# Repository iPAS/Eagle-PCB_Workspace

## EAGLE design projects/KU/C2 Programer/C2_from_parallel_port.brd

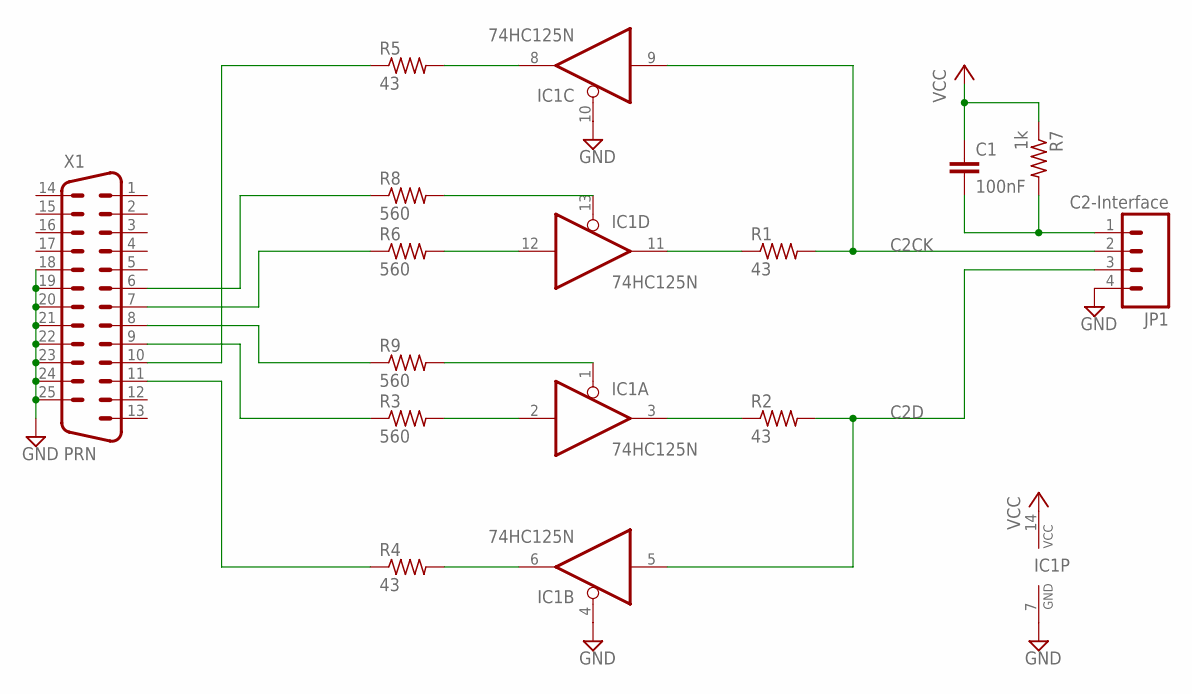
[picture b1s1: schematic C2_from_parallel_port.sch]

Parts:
C1: 100nF; RCL_C050-025X075
IC1: 74HC125N; DIL14
JP1: C2-Interface; MOLEX-1X4
R1, R2, R4, R5: 43; RCL_0204V
R3, R6, R8, R9: 560; RCL_0204V
R7: 1k; RCL_0204V
X1: PRN; M25D

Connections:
C2CK: IC1.9 (I), JP1.2, R1.2
C2D: IC1.5 (I), JP1.3, R2.2
GND: IC1.4 (OE), IC1.7 (GND), IC1.10 (OE), JP1.4, X1.18, X1.19, X1.20, X1.21, X1.22, X1.23, X1.24, X1.25
unnamed: IC1.8 (O), R5.2
unnamed: IC1.13 (OE), R8.2
unnamed: IC1.12 (I), R6.2
unnamed: IC1.1 (OE), R9.2
unnamed: IC1.2 (I), R3.2
unnamed: IC1.6 (O), R4.2
unnamed: R8.1, X1.6
unnamed: R6.1, X1.7
unnamed: R9.1, X1.8
unnamed: R3.1, X1.9
unnamed: R4.1, X1.11
unnamed: R5.1, X1.10
unnamed: IC1.11 (O), R1.1
unnamed: IC1.3 (O), R2.1
unnamed: C1.2, JP1.1, R7.2
VCC: C1.1, IC1.14 (VCC), R7.1

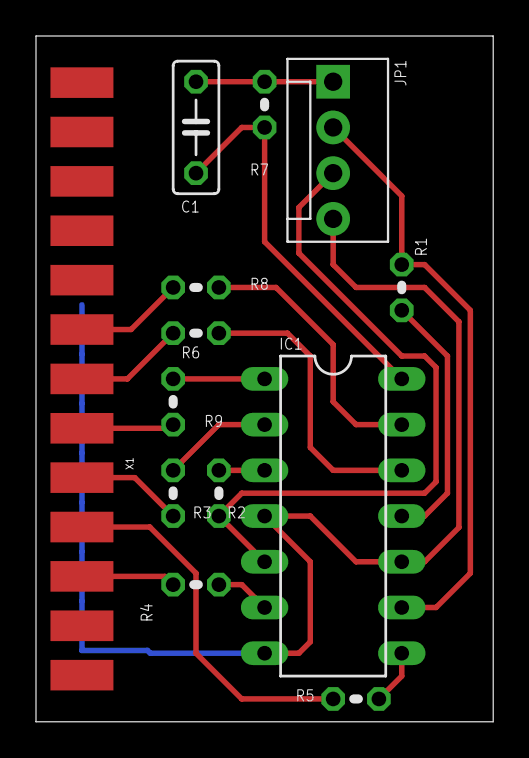
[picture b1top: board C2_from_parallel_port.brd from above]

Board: 2 copper layers, 25.4 x 38.1 mm, 13 parts (0 on the bottom side), 19 nets.

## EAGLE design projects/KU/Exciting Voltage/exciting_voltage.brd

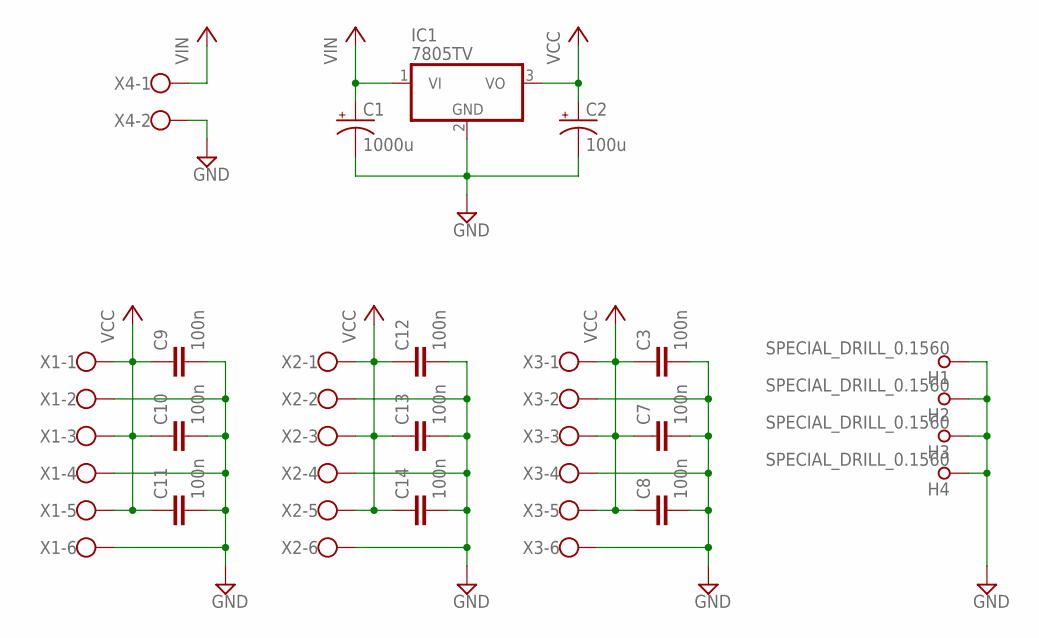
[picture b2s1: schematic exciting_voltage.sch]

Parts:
C1: 1000u; RCL_E5-13
C2: 100u; RCL_E2,5-7
C3, C7, C8, C9, C10, C11, C12, C13, C14: 100n; RCL_C050-025X075
H1, H2, H3, H4: SPECIAL_DRILL_0.1560; PAD_0.1560
IC1: 7805TV; TO220V
X1, X2, X3: 5EHDRC-6P
X4: 5EHDRC-2P

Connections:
GND: C1.-, C2.-, C3.2, C7.2, C8.2, C9.2, C10.2, C11.2, C12.2, C13.2, C14.2, H1.1, H2.1, H3.1, H4.1, IC1.2 (GND), X1.2, X1.4, X1.6, X2.2, X2.4, X2.6, X3.2, X3.4, X3.6, X4.2
VCC: C2.+, C3.1, C7.1, C8.1, C9.1, C10.1, C11.1, C12.1, C13.1, C14.1, IC1.3 (VO), X1.1, X1.3, X1.5, X2.1, X2.3, X2.5, X3.1, X3.3, X3.5
VIN: C1.+, IC1.1 (VI), X4.1

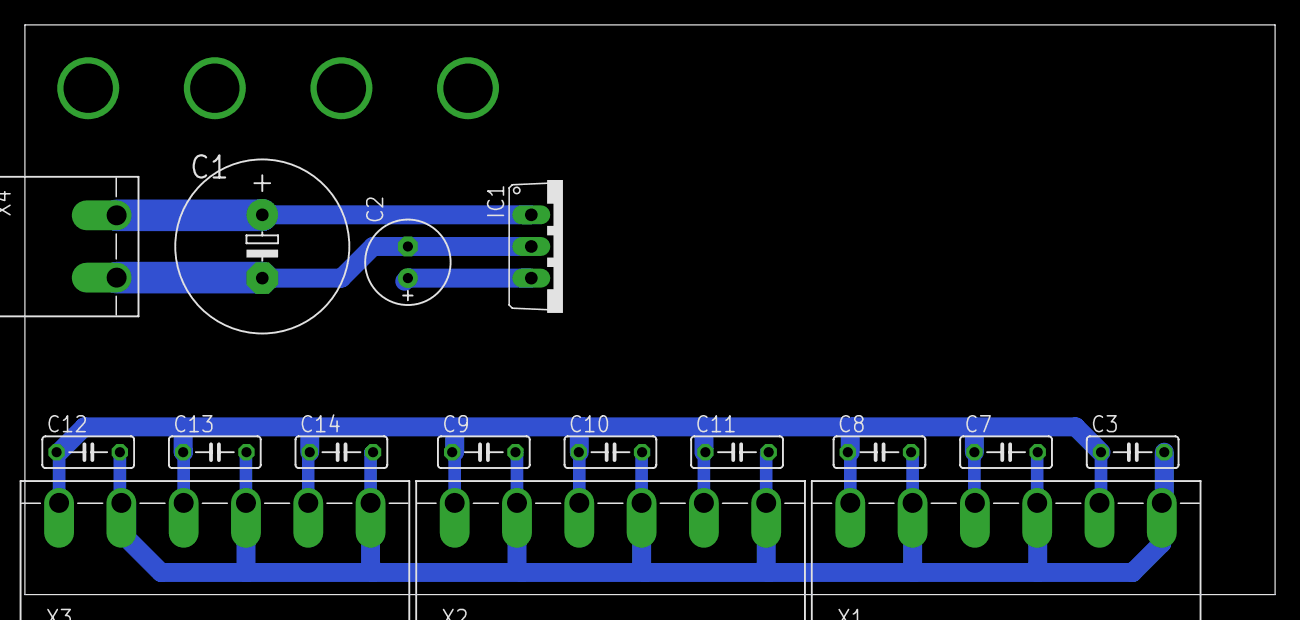
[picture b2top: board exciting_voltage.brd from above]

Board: 2 copper layers, 100.3 x 45.7 mm, 20 parts (0 on the bottom side), 3 nets.

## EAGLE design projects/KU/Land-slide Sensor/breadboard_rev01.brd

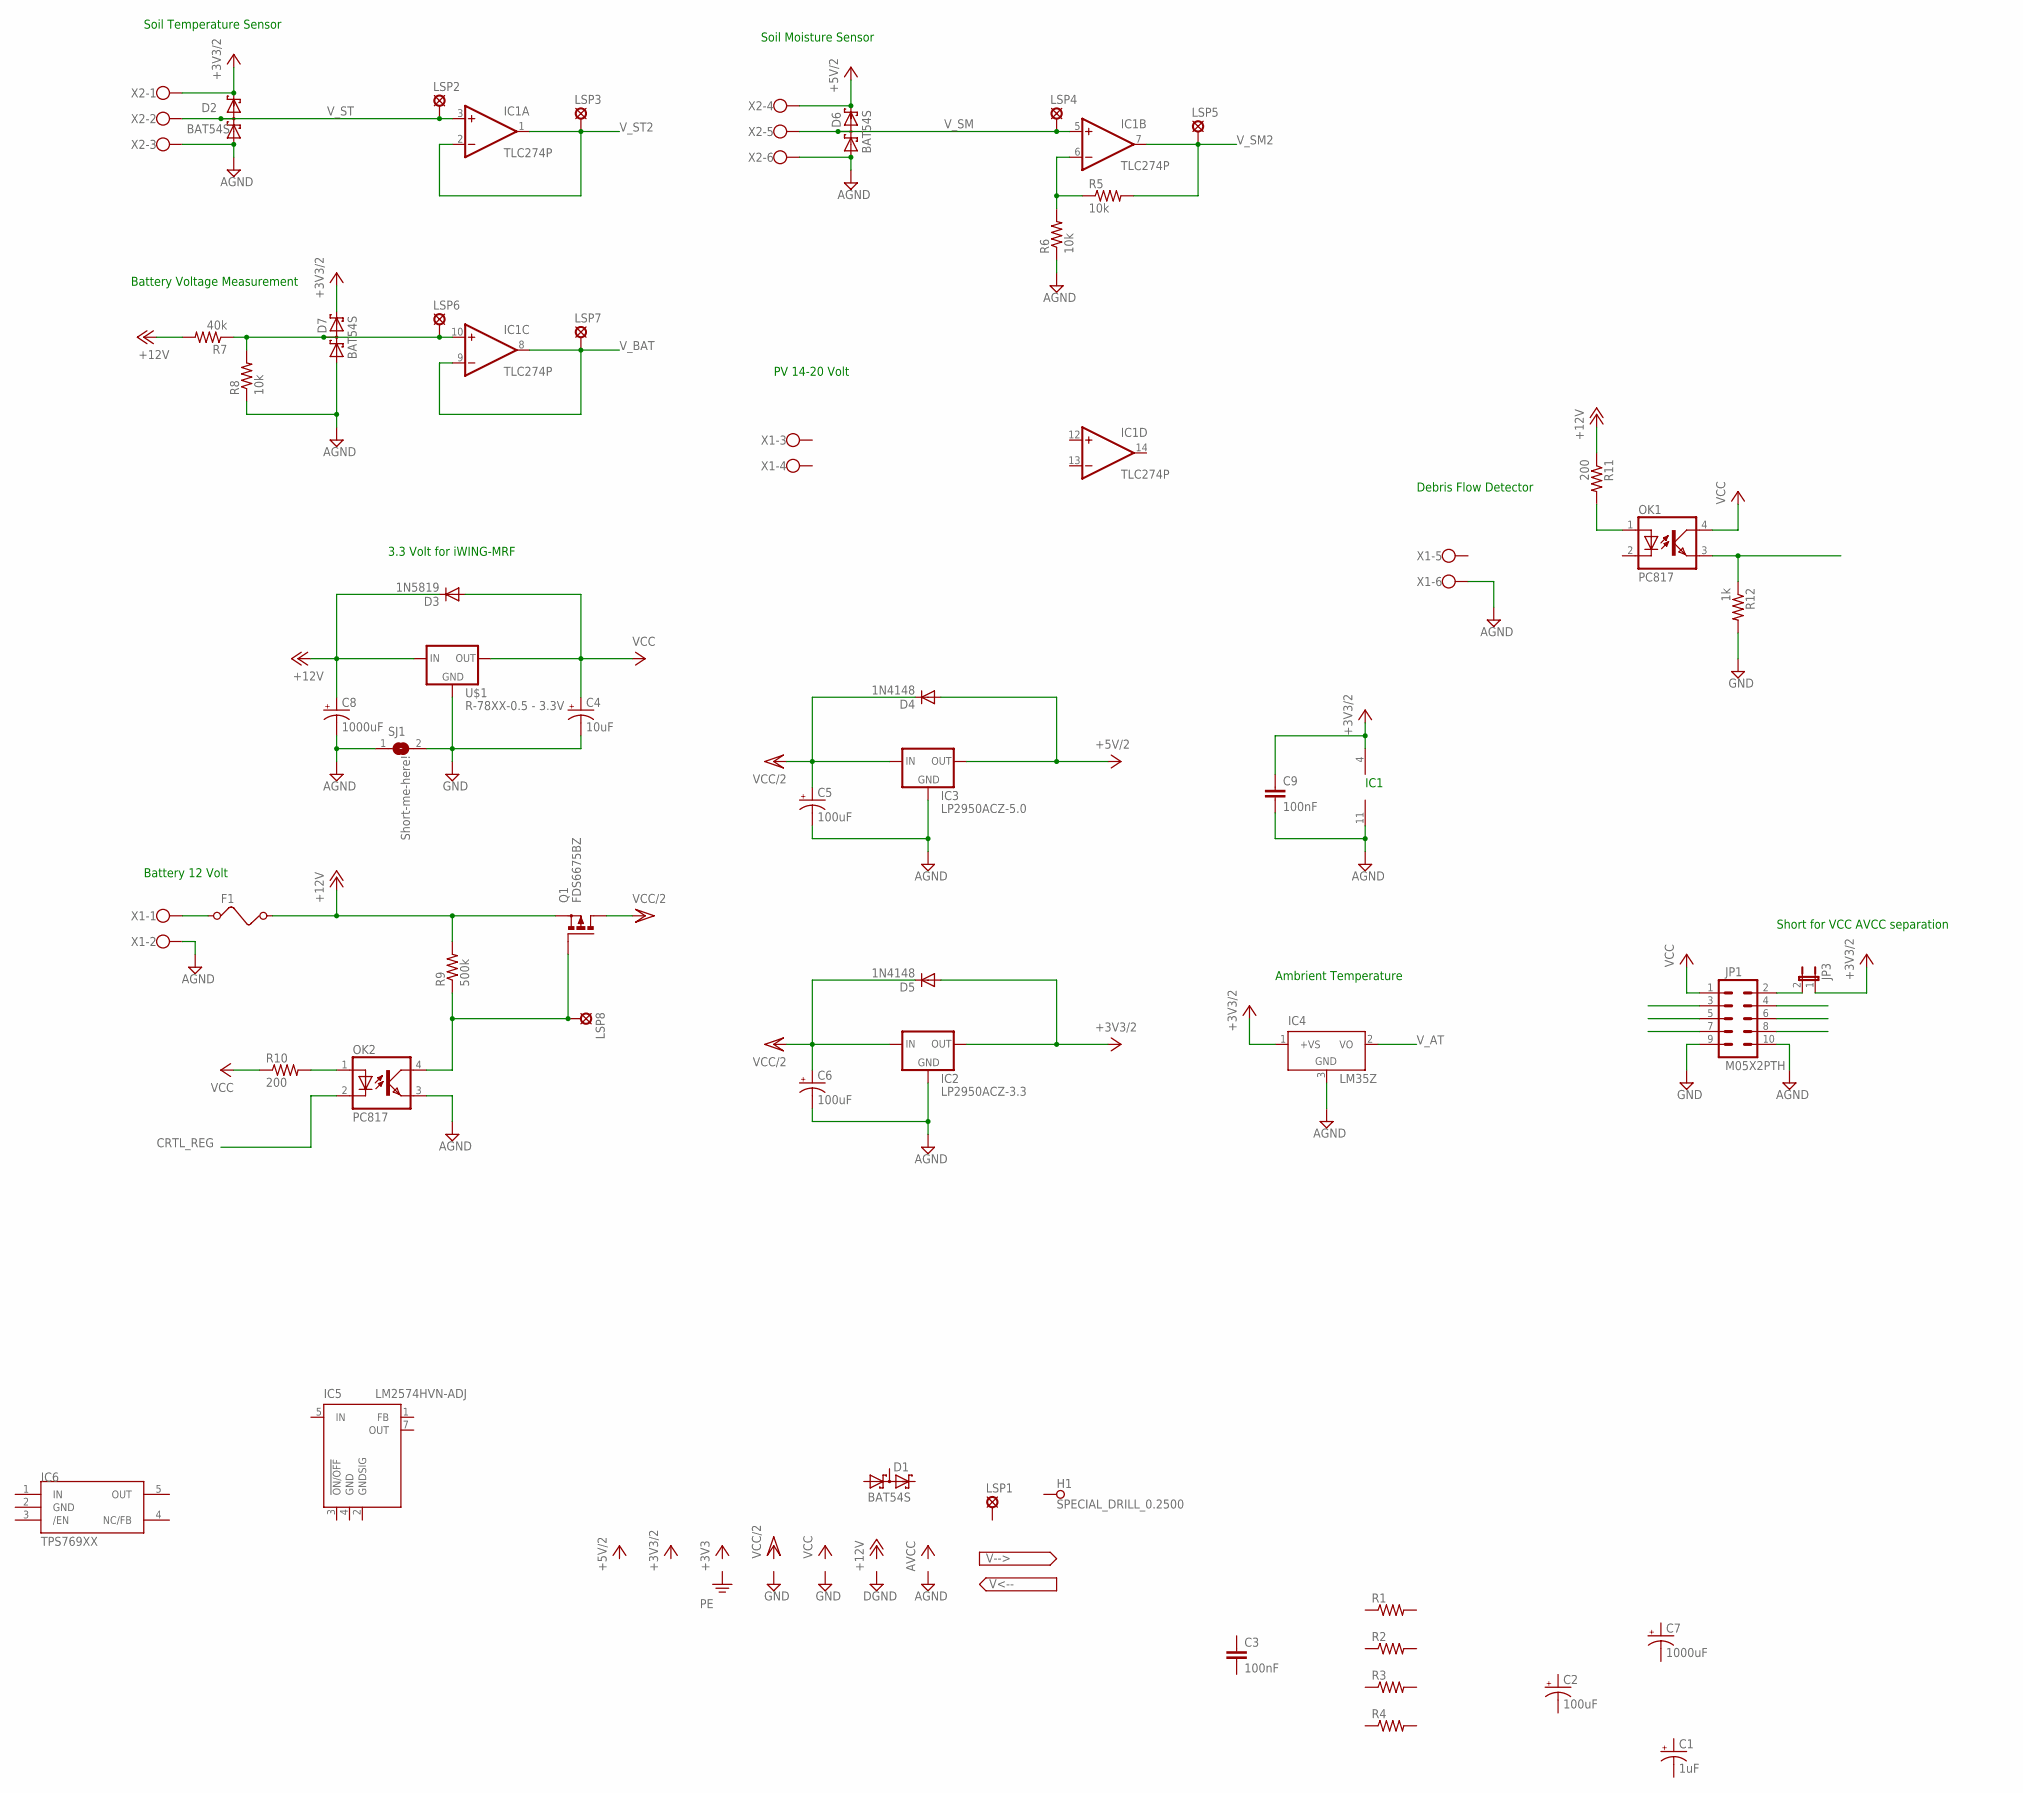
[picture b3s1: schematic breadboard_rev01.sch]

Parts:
C1: 1uF; RCL_E2-5
C2, C5, C6: 100uF; RCL_E2,5-7
C3, C9: 100nF; RCL_C050-025X075
C4: 10uF; RCL_E2,5-7
C7, C8: 1000uF; RCL_E5-13
D1, D2, D6, D7: BAT54S; SOT23
D3: 1N5819; DO41-10
D4, D5: 1N4148; DO35-10
F1: FUSE
H1: SPECIAL_DRILL_0.2500; PAD_0.2500
IC1: TLC274P; DIL14
IC2: LP2950ACZ-3.3; TO92
IC3: LP2950ACZ-5.0; TO92
IC4: LM35Z; TO92
IC5: LM2574HVN-ADJ; DIL08
IC6: TPS769XX; SOT23-5L
JP1: M05X2PTH; AVR_ICSP
JP3: JP1E; JUMPER_JP1
LSP1, LSP2, LSP3, LSP4, LSP5, LSP6, LSP7, LSP8: LSP13
OK1: PC817; DIL04
OK2: PC817; DIL04; MPN PC817X4J000F
Q1: FDS6675BZ; SO-08
R1, R2, R3, R4: RCL_R-US_0204/7; RCL_0204/7
R5, R6, R8: 10k; RCL_0204/7
R7: 40k; RCL_0204/7
R9: 500k; RCL_0204/7
R10, R11: 200; RCL_0204/7
R12: 1k; RCL_0204/7
SJ1: Short-me-here!; SJ
U$1: R-78XX-0.5 - 3.3V; SIP3
X1, X2: 5EHDRC-6P

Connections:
+3V3/2: C9.1, D2.3 (C2), D5.A, D7.3 (C2), IC1.4 (V+), IC2.1 (OUT), IC4.1 (+VS), JP3.1, X2.1
+5V/2: D4.A, D6.3 (C2), IC3.1 (OUT), X2.4
+12V: C8.+, F1.2, Q1.1 (S), Q1.2 (S), Q1.3 (S), R7.2, R9.2, R11.1, U$1.1 (IN)
AGND: C5.-, C6.-, C8.-, C9.2, D2.1 (A1), D6.1 (A1), D7.1 (A1), IC1.11 (V-), IC2.2 (GND), IC3.2 (GND), IC4.3 (GND), JP1.10, OK2.3 (EMIT), R6.1, R8.1, SJ1.1, X1.2, X1.6, X2.3, X2.6
CRTL_REG: OK2.2 (C)
GND: C4.-, IC5.4 (GND), IC6.2 (GND), JP1.9, R12.2, SJ1.2, U$1.2 (GND)
IN: IC6.1 (IN)
unnamed: D7.2 (C1A2), IC1.10 (+IN), LSP6.MP, R7.1, R8.2
unnamed: F1.1, X1.1
unnamed: IC1.6 (-IN), R5.1, R6.2
unnamed: LSP8.MP, OK2.4 (COL), Q1.4 (G), R9.1
unnamed: JP1.2, JP3.2
unnamed: OK1.1 (A), R11.2
unnamed: OK2.1 (A), R10.2
unnamed: OK1.3 (EMIT), R12.1
OUT: IC6.5 (OUT)
VCC: C4.+, JP1.1, OK1.4 (COL), R10.1, U$1.3 (OUT)
VCC/2: C5.+, C6.+, D4.C, D5.C, IC2.3 (IN), IC3.3 (IN), Q1.5 (D), Q1.6 (D), Q1.7 (D), Q1.8 (D)
V_AT: IC4.2 (VO)
V_BAT: IC1.8 (OUT), IC1.9 (-IN), LSP7.MP
V_SM: D6.2 (C1A2), IC1.5 (+IN), LSP4.MP, X2.5
V_SM2: IC1.7 (OUT), LSP5.MP, R5.2
V_ST: D2.2 (C1A2), IC1.3 (+IN), LSP2.MP, X2.2
V_ST2: IC1.1 (OUT), IC1.2 (-IN), LSP3.MP

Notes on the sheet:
Soil Moisture Sensor
Soil Temperature Sensor
Battery 12 Volt
PV 14-20 Volt
Debris Flow Detector
Ambrient Temperature
IC1
3.3 Volt for iWING-MRF
Short for VCC AVCC separation
Battery Voltage Measurement

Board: 2 copper layers, 53 parts (0 on the bottom side), 20 nets, no tracks yet.

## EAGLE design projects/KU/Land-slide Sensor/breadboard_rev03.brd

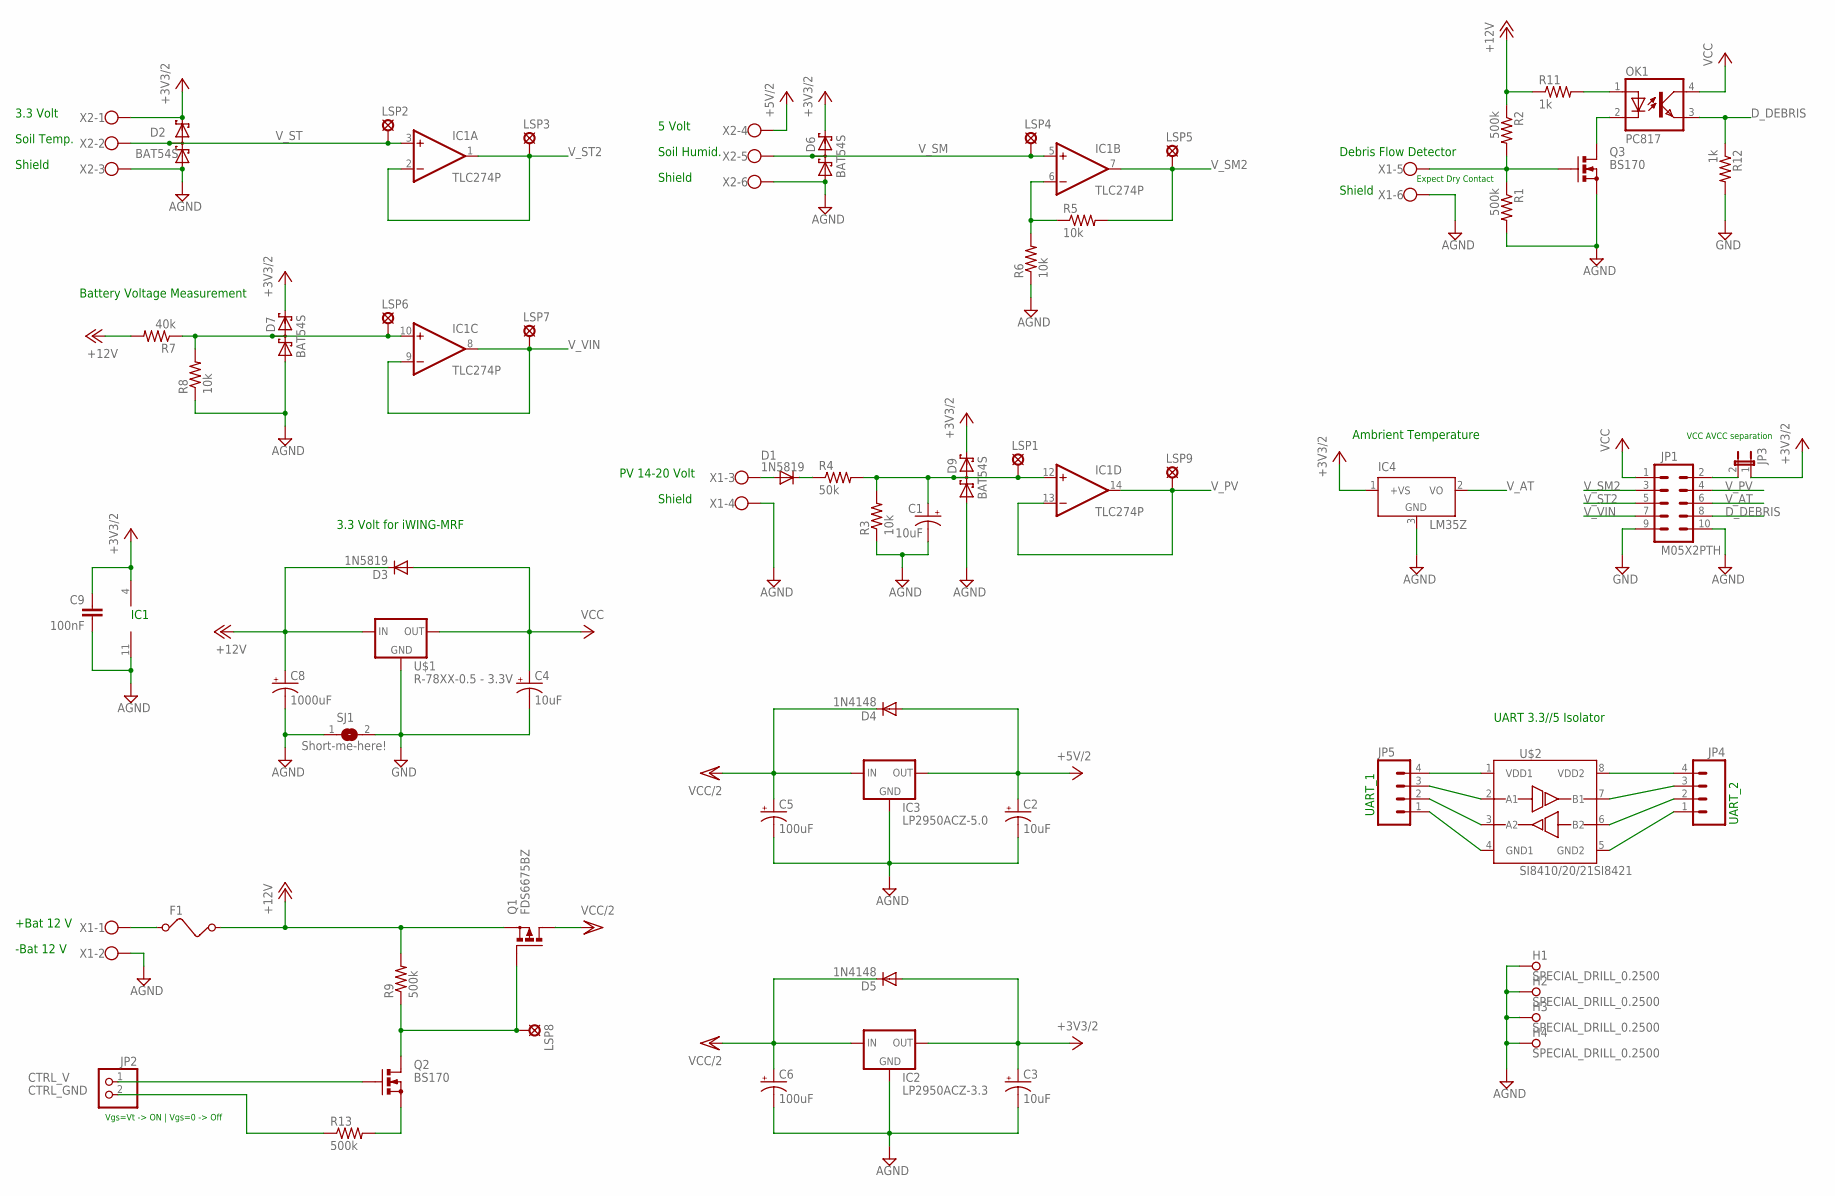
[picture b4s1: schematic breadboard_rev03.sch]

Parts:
C1, C2, C3, C4: 10uF; RCL_E2,5-7
C5, C6: 100uF; RCL_E2,5-7
C8: 1000uF; RCL_E5-13
C9: 100nF; RCL_C050-025X075
D1, D3: 1N5819; DO41-10
D2, D6, D7, D9: BAT54S; SOT23
D4, D5: 1N4148; DO35-10
F1: FUSE
H1, H2, H3, H4: SPECIAL_DRILL_0.2500; PAD_0.2500
IC1: TLC274P; DIL14
IC2: LP2950ACZ-3.3; TO92
IC3: LP2950ACZ-5.0; TO92
IC4: LM35Z; TO92
JP1: M05X2PTH; AVR_ICSP
JP2: PINHD-1X2; 1X02
JP3: JP1E; JUMPER_JP1
JP4, JP5: M04POLAR; MOLEX-1X4
LSP1, LSP2, LSP3, LSP4, LSP5, LSP6, LSP7, LSP8, LSP9: LSP13
OK1: PC817; DIL04
Q1: FDS6675BZ; SO-08
Q2, Q3: BS170; SOT54E
R1, R2, R9, R13: 500k; RCL_0204/7
R3, R5, R6, R8: 10k; RCL_0204/7
R4: 50k; RCL_0204/7
R7: 40k; RCL_0204/7
R11, R12: 1k; RCL_0204/7
SJ1: Short-me-here!; SJ
U$1: R-78XX-0.5 - 3.3V; SIP3
U$2: SI8410/20/21SI8421; SO-08
X1, X2: 5EHDRC-6P

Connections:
+3V3/2: C3.+, C9.1, D2.3 (C2), D5.A, D6.3 (C2), D7.3 (C2), D9.3 (C2), IC1.4 (V+), IC2.1 (OUT), IC4.1 (+VS), JP3.1, X2.1
+5V/2: C2.+, D4.A, IC3.1 (OUT), X2.4
+12V: C8.+, F1.2, Q1.1 (S), Q1.2 (S), Q1.3 (S), R2.1, R7.2, R9.2, R11.1, U$1.1 (IN)
AGND: C1.-, C2.-, C3.-, C5.-, C6.-, C8.-, C9.2, D2.1 (A1), D6.1 (A1), D7.1 (A1), D9.1 (A1), H1.1, H2.1, H3.1, H4.1, IC1.11 (V-), IC2.2 (GND), IC3.2 (GND), IC4.3 (GND), JP1.10, Q3.S, R1.2, R3.1, R6.1, R8.1, SJ1.1, X1.2, X1.4, X1.6, X2.3, X2.6
CTRL_GND: JP2.2, R13.1
CTRL_V: JP2.1, Q2.G
D_DEBRIS: JP1.8, OK1.3 (EMIT), R12.1
GND: C4.-, JP1.9, R12.2, SJ1.2, U$1.2 (GND)
unnamed: D7.2 (C1A2), IC1.10 (+IN), LSP6.MP, R7.1, R8.2
unnamed: F1.1, X1.1
unnamed: IC1.6 (-IN), R5.1, R6.2
unnamed: LSP8.MP, Q1.4 (G), Q2.D, R9.1
unnamed: JP1.2, JP3.2
unnamed: OK1.1 (A), R11.2
unnamed: Q2.S, R13.2
unnamed: OK1.2 (C), Q3.D
unnamed: Q3.G, R1.1, R2.2, X1.5
unnamed: D1.A, X1.3
unnamed: JP4.4, U$2.8 (VDD2)
unnamed: D1.C, R4.1
unnamed: JP4.1, U$2.5 (GND2)
unnamed: JP5.4, U$2.1 (VDD1)
unnamed: JP5.3, U$2.2 (A1)
unnamed: C1.+, D9.2 (C1A2), IC1.12 (+IN), LSP1.MP, R3.2, R4.2
unnamed: JP5.2, U$2.3 (A2)
unnamed: JP5.1, U$2.4 (GND1)
RX: JP4.3, U$2.7 (B1)
TX: JP4.2, U$2.6 (B2)
VCC: C4.+, JP1.1, OK1.4 (COL), U$1.3 (OUT)
VCC/2: C5.+, C6.+, D4.C, D5.C, IC2.3 (IN), IC3.3 (IN), Q1.5 (D), Q1.6 (D), Q1.7 (D), Q1.8 (D)
V_AT: IC4.2 (VO), JP1.6
V_PV: IC1.13 (-IN), IC1.14 (OUT), JP1.4, LSP9.MP
V_SM: D6.2 (C1A2), IC1.5 (+IN), LSP4.MP, X2.5
V_SM2: IC1.7 (OUT), JP1.3, LSP5.MP, R5.2
V_ST: D2.2 (C1A2), IC1.3 (+IN), LSP2.MP, X2.2
V_ST2: IC1.1 (OUT), IC1.2 (-IN), JP1.5, LSP3.MP
V_VIN: IC1.8 (OUT), IC1.9 (-IN), JP1.7, LSP7.MP

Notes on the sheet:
+Bat 12 V
PV 14-20 Volt
Debris Flow Detector
Ambrient Temperature
IC1
3.3 Volt for iWING-MRF
VCC AVCC separation
Battery Voltage Measurement
Vgs=Vt -> ON | Vgs=0 -> Off
Expect Dry Contact
UART 3.3//5 Isolator
UART_1
UART_2
3.3 Volt
Soil Temp.
Shield
5 Volt
Soil Humid.
-Bat 12 V

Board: 2 copper layers, 60 parts (0 on the bottom side), 37 nets, no tracks yet.

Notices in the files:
parts and their libraries:
SparkFun-Connectors: Licensing: CC v3.0 Share-Alike You are welcome to use this library for commercial purposes.
